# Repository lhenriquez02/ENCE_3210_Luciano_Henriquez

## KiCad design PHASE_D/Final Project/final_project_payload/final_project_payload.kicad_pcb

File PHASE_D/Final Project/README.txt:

In the 3d model of the PCB, you'll notice that one of the components clips the pin sockets of the Arduino, but this would not happen if the pin sockets were instead pin headers like when we designed our thermos pro shield. Unfortunately, I was unable to change the 3d model for the Arduino uno pin components, as I could not find a way to interact with the component on the PCB editor at all. Rest assured, this would not be an issue if the pin sockets were headers instead. We have direct control over the components we choose to add to the board, so this in principle would not arise if the design were sent to the fab house.

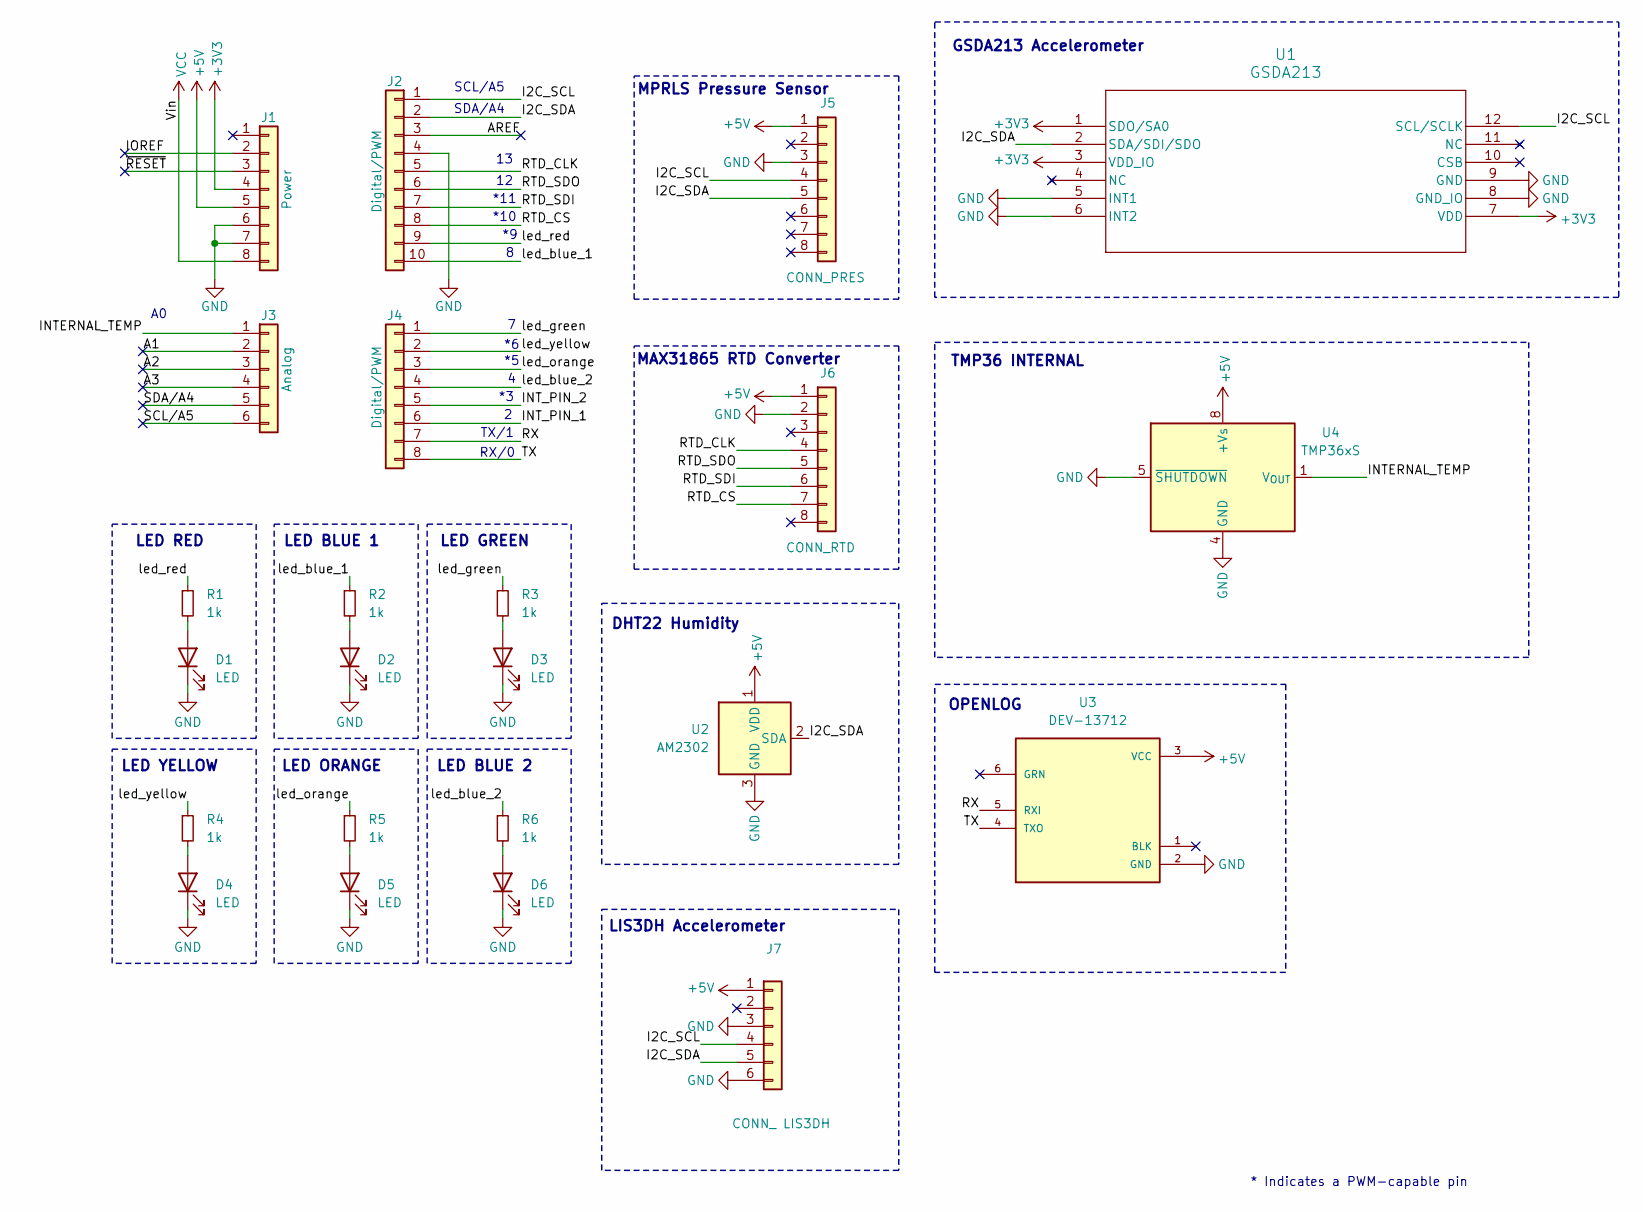
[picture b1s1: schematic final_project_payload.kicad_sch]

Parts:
D1, D2, D3, D4, D5, D6: LED; LED_D5.0mm
J1: Power; PinSocket_1x08_P2.54mm_Vertical
J2: Digital/PWM; PinSocket_1x10_P2.54mm_Vertical
J3: Analog; PinSocket_1x06_P2.54mm_Vertical
J4: Digital/PWM; PinSocket_1x08_P2.54mm_Vertical
J5: CONN_PRES; PinSocket_1x08_P2.54mm_Vertical
J6: CONN_RTD; PinSocket_1x08_P2.54mm_Vertical
J7: CONN_ LIS3DH; PinSocket_1x06_P2.54mm_Vertical
R1, R2, R3, R4, R5, R6: 1k; R_Axial_DIN0207_L6.3mm_D2.5mm_P10.16mm_Horizontal
U1: GSDA213; LGA12_GAS
U2: AM2302; ASAIR_AM2302_P2.54mm_Vertical
U3: DEV-13712; MODULE_DEV-13712; PARTREV v15
U4: TMP36xS; SOIC-8_3.9x4.9mm_P1.27mm

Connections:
+3V3: J1.4, U1.1 (SDO/SA0), U1.3 (VDD_IO), U1.7 (VDD)
+5V: J1.5, J5.1, J6.1, J7.1, U2.1 (VDD), U3.3 (VCC), U4.8 (+Vs)
/A1: J3.2
/A2: J3.3
/A3: J3.4
/AREF: J2.3
/I2C_SCL: J2.1, J5.4, J7.4, U1.12 (SCL/SCLK)
/I2C_SDA: J2.2, J5.5, J7.5, U1.2 (SDA/SDI/SDO), U2.2 (SDA)
/INTERNAL_TEMP: J3.1, U4.1 (V_{OUT})
/INT_PIN_1: J4.6
/INT_PIN_2: J4.5
/IOREF: J1.2
/RTD_CLK: J2.5, J6.4
/RTD_CS: J2.8, J6.7
/RTD_SDI: J2.7, J6.6
/RTD_SDO: J2.6, J6.5
/RX: J4.7, U3.5 (RXI)
/SCL/A5: J3.6
/SDA/A4: J3.5
/TX: J4.8, U3.4 (TXO)
/led_blue_1: J2.10, R2.1
/led_blue_2: J4.4, R6.1
/led_green: J4.1, R3.1
/led_orange: J4.3, R5.1
/led_red: J2.9, R1.1
/led_yellow: J4.2, R4.1
/~RESET: J1.3
GND: D1.1 (K), D2.1 (K), D3.1 (K), D4.1 (K), D5.1 (K), D6.1 (K), J1.6, J1.7, J2.4, J5.3, J6.2, J7.3, J7.6, U1.5 (INT1), U1.6 (INT2), U1.8 (GND_IO), U1.9 (GND), U2.3 (GND), U2.4 (GND), U3.2 (GND), U4.4 (GND), U4.5 (~SHUTDOWN)
unnamed: D1.2 (A), R1.2
unnamed: D2.2 (A), R2.2
unnamed: D3.2 (A), R3.2
unnamed: D4.2 (A), R4.2
unnamed: D5.2 (A), R5.2
unnamed: D6.2 (A), R6.2
VCC: J1.8

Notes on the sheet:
LED GREEN
DHT22 Humidity
LED BLUE 1
TMP36 INTERNAL
LED RED
MAX31865 RTD Converter
*10
RX/0
OPENLOG
LED BLUE 2
LED ORANGE
SCL/A5
MPRLS Pressure Sensor
LIS3DH Accelerometer
GSDA213 Accelerometer
*11
LED YELLOW
* Indicates a PWM-capable pin
TX/1
SDA/A4

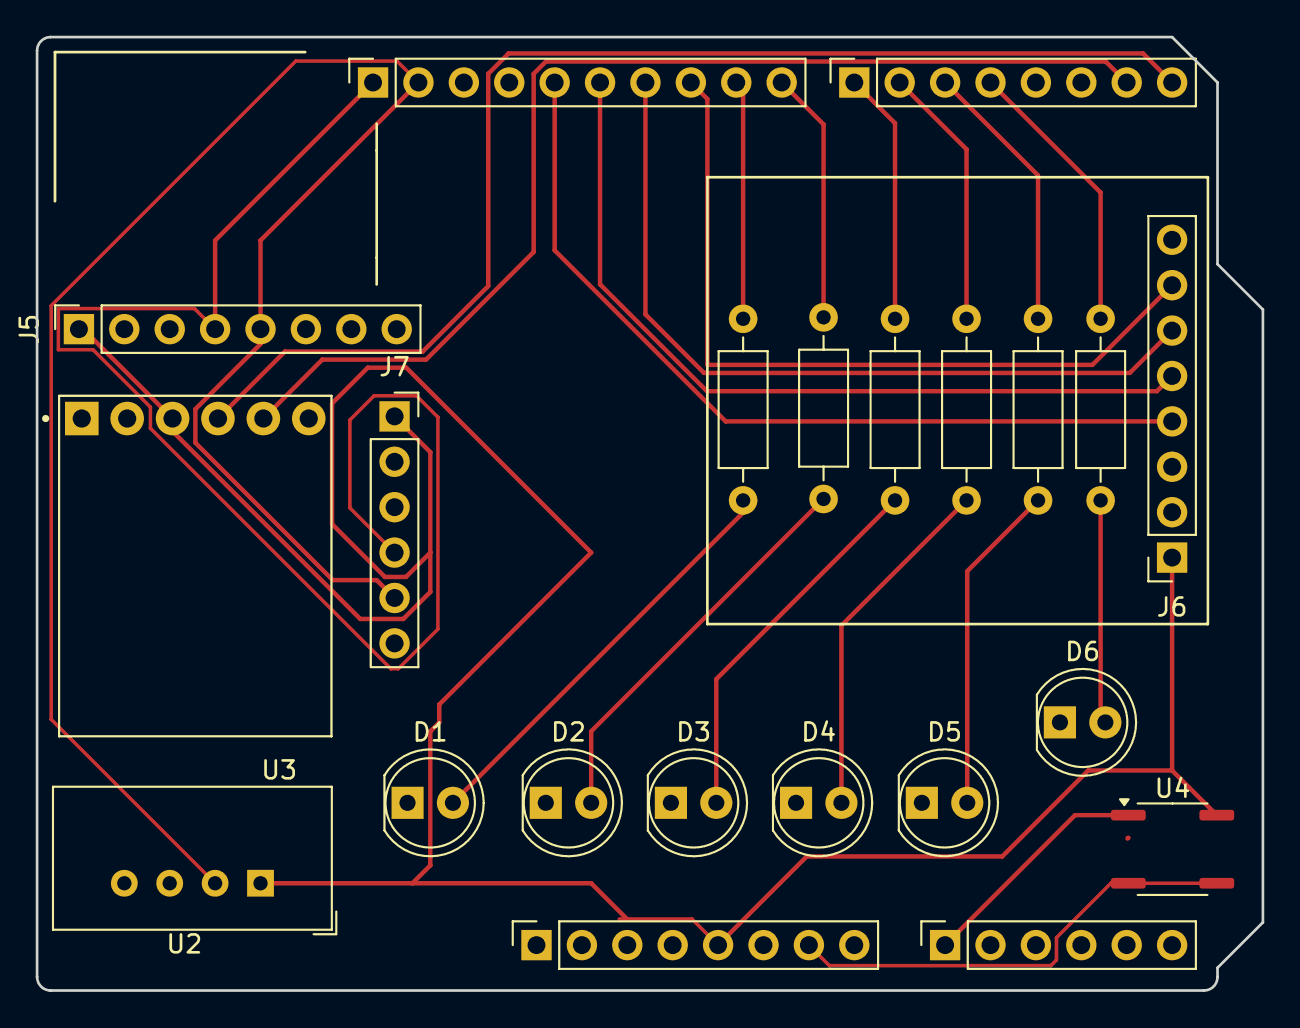
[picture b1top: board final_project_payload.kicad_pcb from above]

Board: 2 copper layers, 68.6 x 53.3 mm, 22 parts (0 on the bottom side), 23 nets.

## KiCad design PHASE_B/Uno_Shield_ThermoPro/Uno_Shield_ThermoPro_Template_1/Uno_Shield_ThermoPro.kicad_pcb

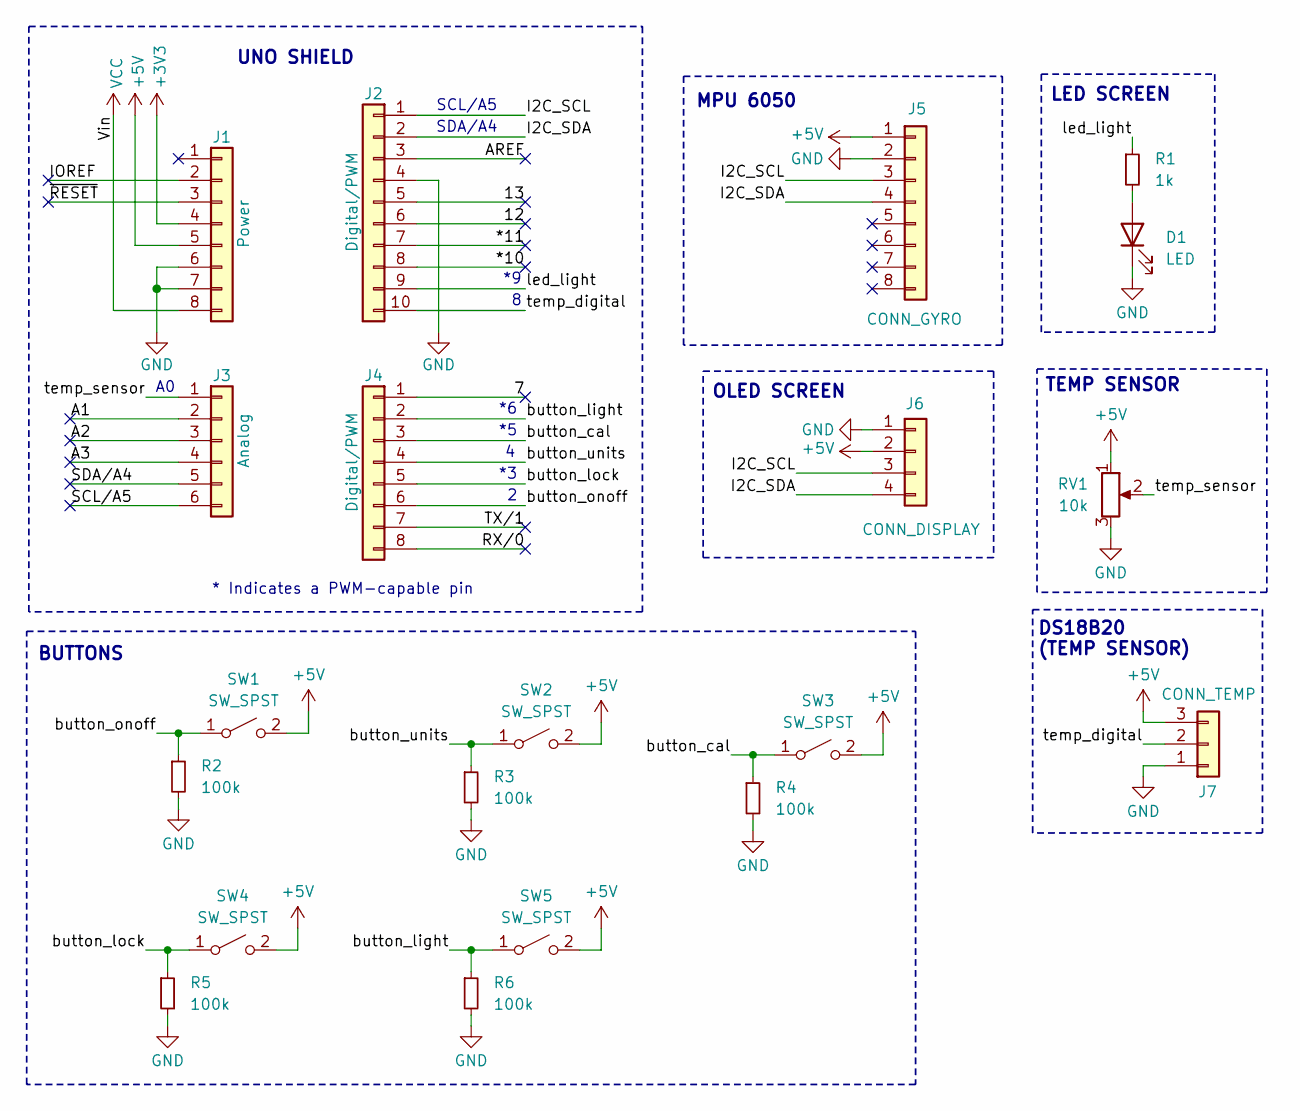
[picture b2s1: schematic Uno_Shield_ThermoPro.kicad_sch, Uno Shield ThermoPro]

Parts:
D1: LED; LED_D5.0mm
J1: Power; PinSocket_1x08_P2.54mm_Vertical
J2: Digital/PWM; PinSocket_1x10_P2.54mm_Vertical
J3: Analog; PinSocket_1x06_P2.54mm_Vertical
J4: Digital/PWM; PinSocket_1x08_P2.54mm_Vertical
J5: CONN_GYRO; PinSocket_1x08_P2.54mm_Vertical
J6: CONN_DISPLAY; PinSocket_1x04_P2.54mm_Vertical
J7: CONN_TEMP; JST_XH_B3B-XH-A_1x03_P2.50mm_Vertical
R1: 1k; R_Axial_DIN0207_L6.3mm_D2.5mm_P10.16mm_Horizontal
R2, R3, R4, R5, R6: 100k; R_Axial_DIN0207_L6.3mm_D2.5mm_P10.16mm_Horizontal
RV1: 10k; Potentiometer_Bourns_3386P_Vertical
SW1, SW2, SW3, SW4, SW5: SW_SPST; SW_PUSH_6mm

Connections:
+3V3: J1.4
+5V: J1.5, J5.1, J6.2, J7.3, RV1.1, SW1.2 (B), SW2.2 (B), SW3.2 (B), SW4.2 (B), SW5.2 (B)
/7: J4.1
/12: J2.6
/13: J2.5
/*10: J2.8
/*11: J2.7
/A1: J3.2
/A2: J3.3
/A3: J3.4
/AREF: J2.3
/I2C_SCL: J2.1, J5.3, J6.3
/I2C_SDA: J2.2, J5.4, J6.4
/IOREF: J1.2
/RX/0: J4.8
/SCL/A5: J3.6
/SDA/A4: J3.5
/TX/1: J4.7
/button_cal: J4.3, R4.1, SW3.1 (A)
/button_light: J4.2, R6.1, SW5.1 (A)
/button_lock: J4.5, R5.1, SW4.1 (A)
/button_onoff: J4.6, R2.1, SW1.1 (A)
/button_units: J4.4, R3.1, SW2.1 (A)
/led_light: J2.9, R1.1
/temp_digital: J2.10, J7.2
/temp_sensor: J3.1, RV1.2
/~RESET: J1.3
GND: D1.1 (K), J1.6, J1.7, J2.4, J5.2, J6.1, J7.1, R2.2, R3.2, R4.2, R5.2, R6.2, RV1.3
unnamed: D1.2 (A), R1.2
VCC: J1.8

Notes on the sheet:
DS18B20 (TEMP SENSOR)
OLED SCREEN
LED SCREEN
TEMP SENSOR
UNO SHIELD
MPU 6050
SCL/A5
SDA/A4
BUTTONS
* Indicates a PWM-capable pin

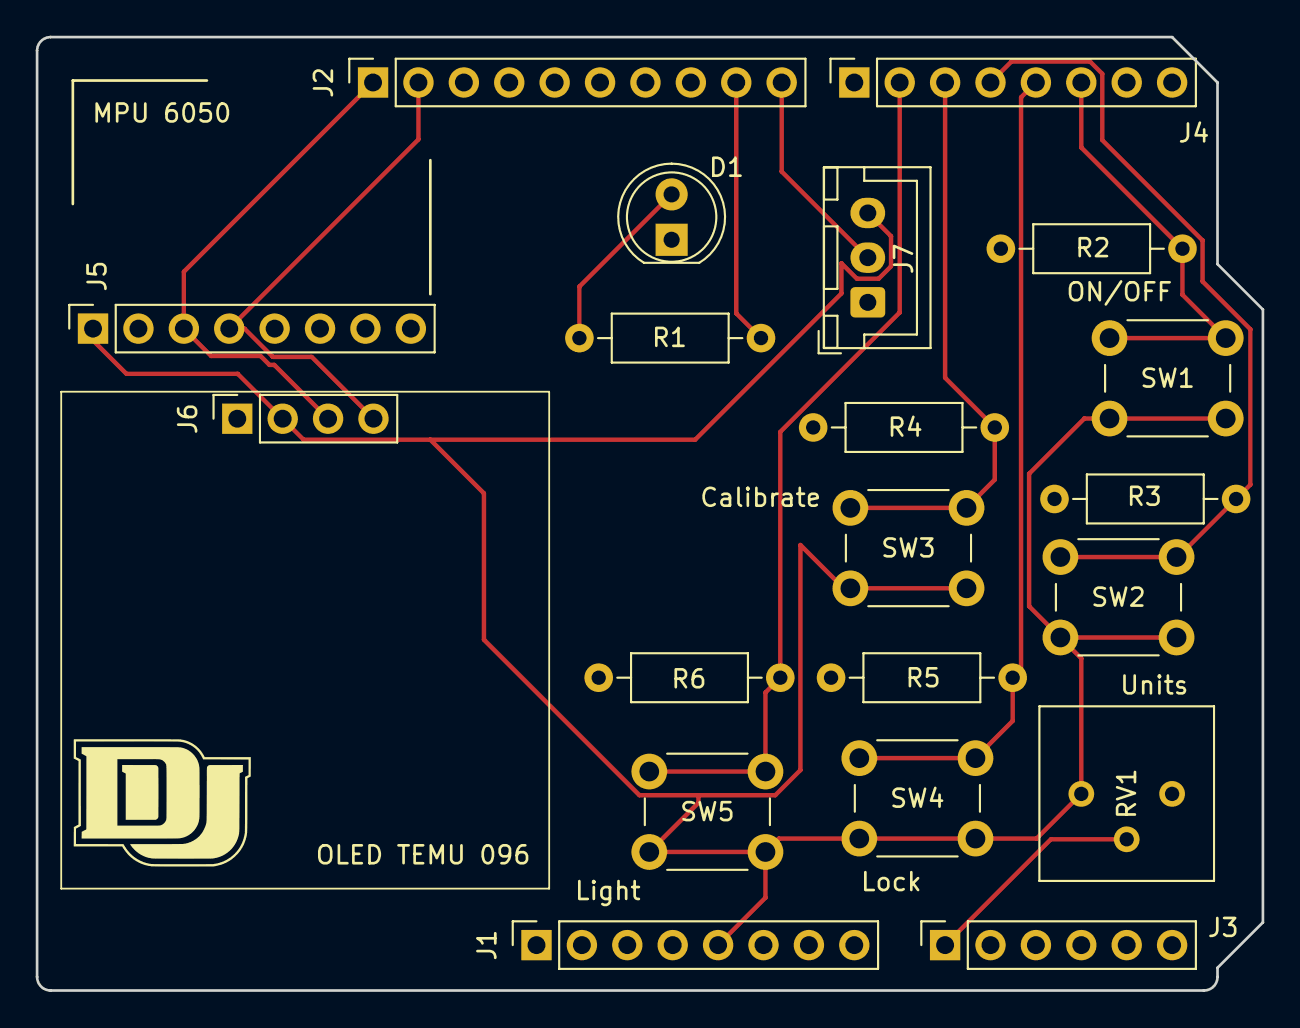
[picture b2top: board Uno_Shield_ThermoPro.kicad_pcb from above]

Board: 2 copper layers, 68.6 x 53.3 mm, 20 parts (0 on the bottom side), 13 nets.

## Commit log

2025-01-10 test
2025-01-10 temp solution to test upload
2025-01-15 Uploaded problem 2 solution
2025-01-15 Uploaded official solution to problem 3
2025-01-15 Uploaded official solution to question 3
2025-01-15 deleted earlier version of solution
2025-01-15 Added solution to problem 4
2025-01-17 Uploaded official solution to question 7
2025-01-17 Uploaded solution to problem 6
2025-01-17 Uploaded solution to problem 5
2025-01-17 Uploaded soultion to problem 1
2025-01-19 Solution to poblem 1 in lab 2 added
2025-01-24 Added solutions to questions 2,3, and 4
2025-01-28 Update problem2lab1soln.ino
    quick fix for optimization
2025-01-28 Added solution to exercise for lab 3
2025-01-28 Update problem3lab2soln.ino
    At the end of the program, I had all lights turning off, when they should turn on. Fixed this
2025-02-03 added template for uno shield
2025-02-04 Uploaded kicad files
2025-02-04 Uploaded kicad files again
2025-02-04 final update to kicad kiles
2025-02-20 Uploaded almost fully complete code for thermo pro shield. Only needs cal button (not sure what that button does)
2025-02-23 Added solutions to lab 4 problems 1,2, and 3, still need to add comments
2025-02-23 Change delay values to make program feel faster
2025-02-27 Update ThermoProNoCal.ino
    Added comments
2025-03-05 Uploaded problem 4
2025-03-06 Added system diagram, I had initially only added code block diagram.
2025-03-07 added block diagram (forgot earlier) for thermo pro code
2025-03-14 Uploaded final project Kicad files
2025-03-14 Added analysis
2025-03-14 added slide show
2025-03-14 Uploaded all project files
2025-03-14 added important read me, please read
2025-03-14 Updated slides
